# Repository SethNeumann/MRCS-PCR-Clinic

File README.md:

# MRCS-PCR-Clinic
## License: Creative Commons Attribution-NonCommercial-ShareAlike

Project board for PCR-NMRA Arduino Programming class by Earl Girbovan and Seth Neumann

The Project Board includes examples of inputs (push buttons,
potentiometers) and outputs (LEDs, an SG90 Servo) that are often
found in model railroad projects.  Since the clinic is about learning
the Arduino Integrated Development Environment (IDE) and learning
the Arduino "Processing" language, the board is offered assembled
so you can start right away without the need to do assembly.
Connectors are provided for the Nano (included with the A&T version),
external power and ground, and the i/o pins not used on the boards.
Pads are provided for an I2C connection if you want to expand your
project using our IOX16 and IOX32.

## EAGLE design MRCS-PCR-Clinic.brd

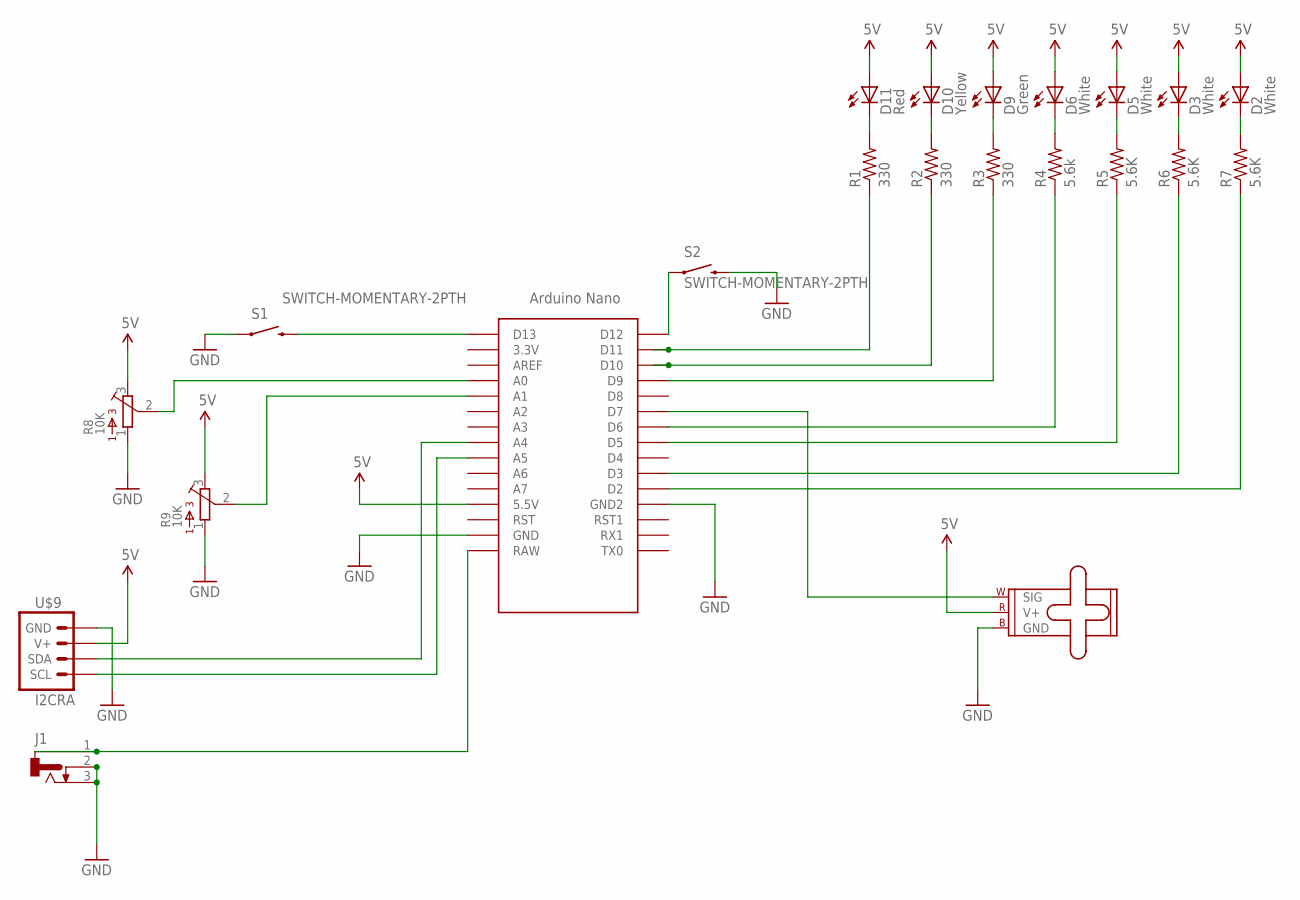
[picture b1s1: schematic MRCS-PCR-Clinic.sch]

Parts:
D2, D3, D5, D6: White; LED3MM
D9: Green; LED3MM
D10: Yellow; LED3MM
D11: Red; LED3MM
J1: CONNECTOR-DC-POWER-RA; DCJ0202
M2: SMALL_SERVO; 1X03
R1, R2, R3: 330; AXIAL-0.4
R4: 5.6k; AXIAL-0.4
R5, R6, R7: 5.6K; AXIAL-0.4
R8, R9: 10K; 3386P
S1, S2: SWITCH-MOMENTARY-2PTH; TACTILE-PTH
U$1: NANO
U$9: I2CRA; I2C

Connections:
5V: D2.A, D3.A, D5.A, D6.A, D9.A, D10.A, D11.A, M2.2 (V+), R8.3, R9.3, U$1.5V (5.5V), U$9.V+
A0: R8.2, U$1.A0
A1: R9.2, U$1.A1
D2: R7.P$1 (1), U$1.D2
D3: R6.P$1 (1), U$1.D3
D5: R5.P$1 (1), U$1.D5
D6: R4.P$1 (1), U$1.D6
D7: M2.1 (SIG), U$1.D7
D9: R3.P$1 (1), U$1.D9
D10: R2.P$1 (1), U$1.D10
D11: R1.P$1 (1), U$1.D11
D12: S2.1, U$1.D12
D13: S1.3 (2), U$1.D13
GND: J1.2, J1.3, M2.3 (GND), R8.1, R9.1, S1.1, S2.3 (2), U$1.GND, U$1.GND1 (GND2), U$9.GND
unnamed: J1.1, U$1.RAW
unnamed: D11.K (C), R1.P$2 (2)
unnamed: D10.K (C), R2.P$2 (2)
unnamed: D9.K (C), R3.P$2 (2)
unnamed: D6.K (C), R4.P$2 (2)
unnamed: D5.K (C), R5.P$2 (2)
unnamed: D3.K (C), R6.P$2 (2)
unnamed: D2.K (C), R7.P$2 (2)
SCL: U$1.A5, U$9.SCL
SDA: U$1.A4, U$9.SDA

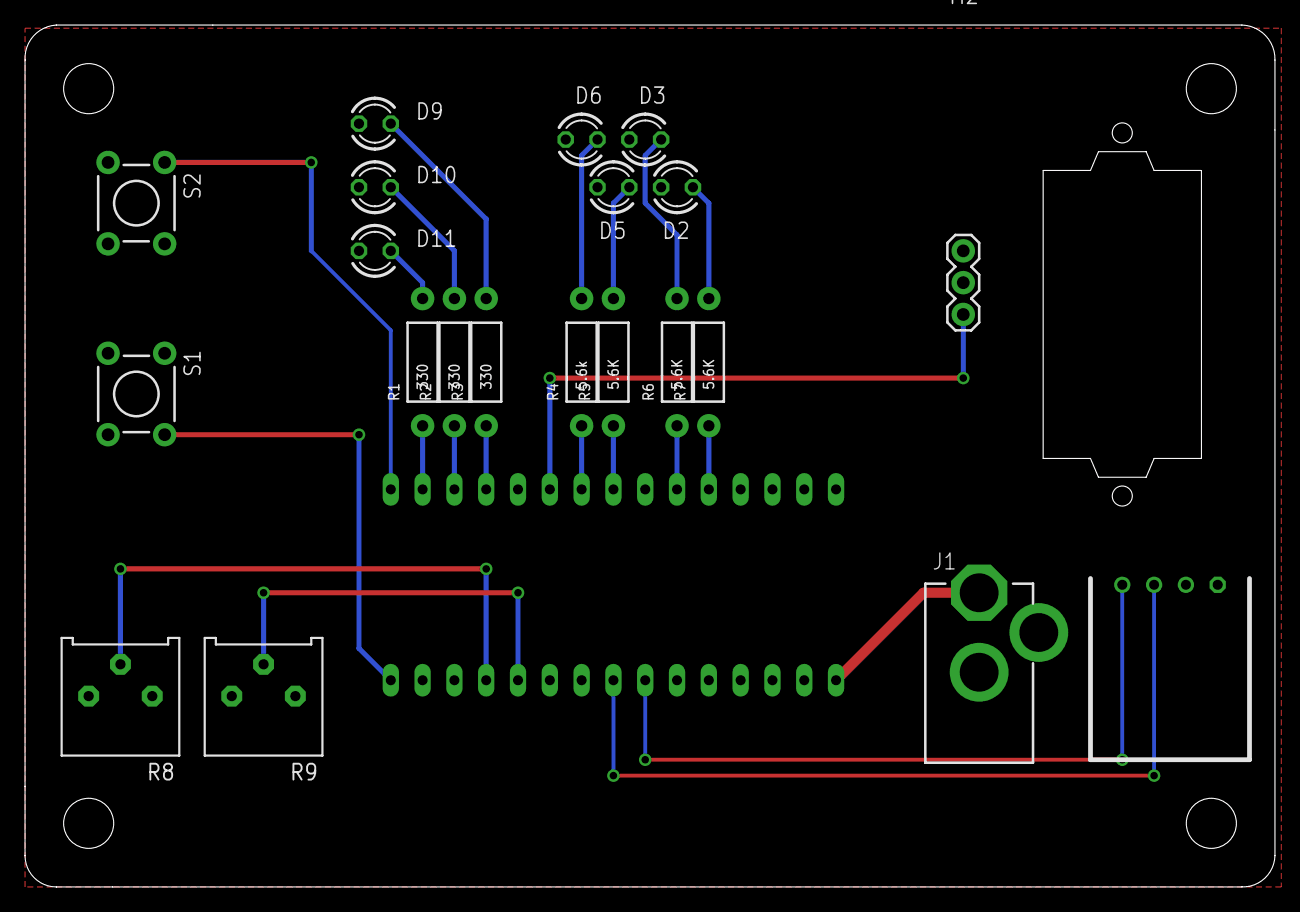
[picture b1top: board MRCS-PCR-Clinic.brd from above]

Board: 2 copper layers, 99.8 x 68.8 mm, 24 parts (0 on the bottom side), 24 nets.

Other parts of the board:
U$10: BOARD-DINRAIL-2.7IN
U$11: SERVO-9G

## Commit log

2019-11-28 code cleanup
2019-11-28 added doc
2020-05-04 updated tags

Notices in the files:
parts and their libraries:
SparkFun-Electromechanical: Licensing: CC v3.0 Share-Alike You are welcome to use this library for commercial purposes.
